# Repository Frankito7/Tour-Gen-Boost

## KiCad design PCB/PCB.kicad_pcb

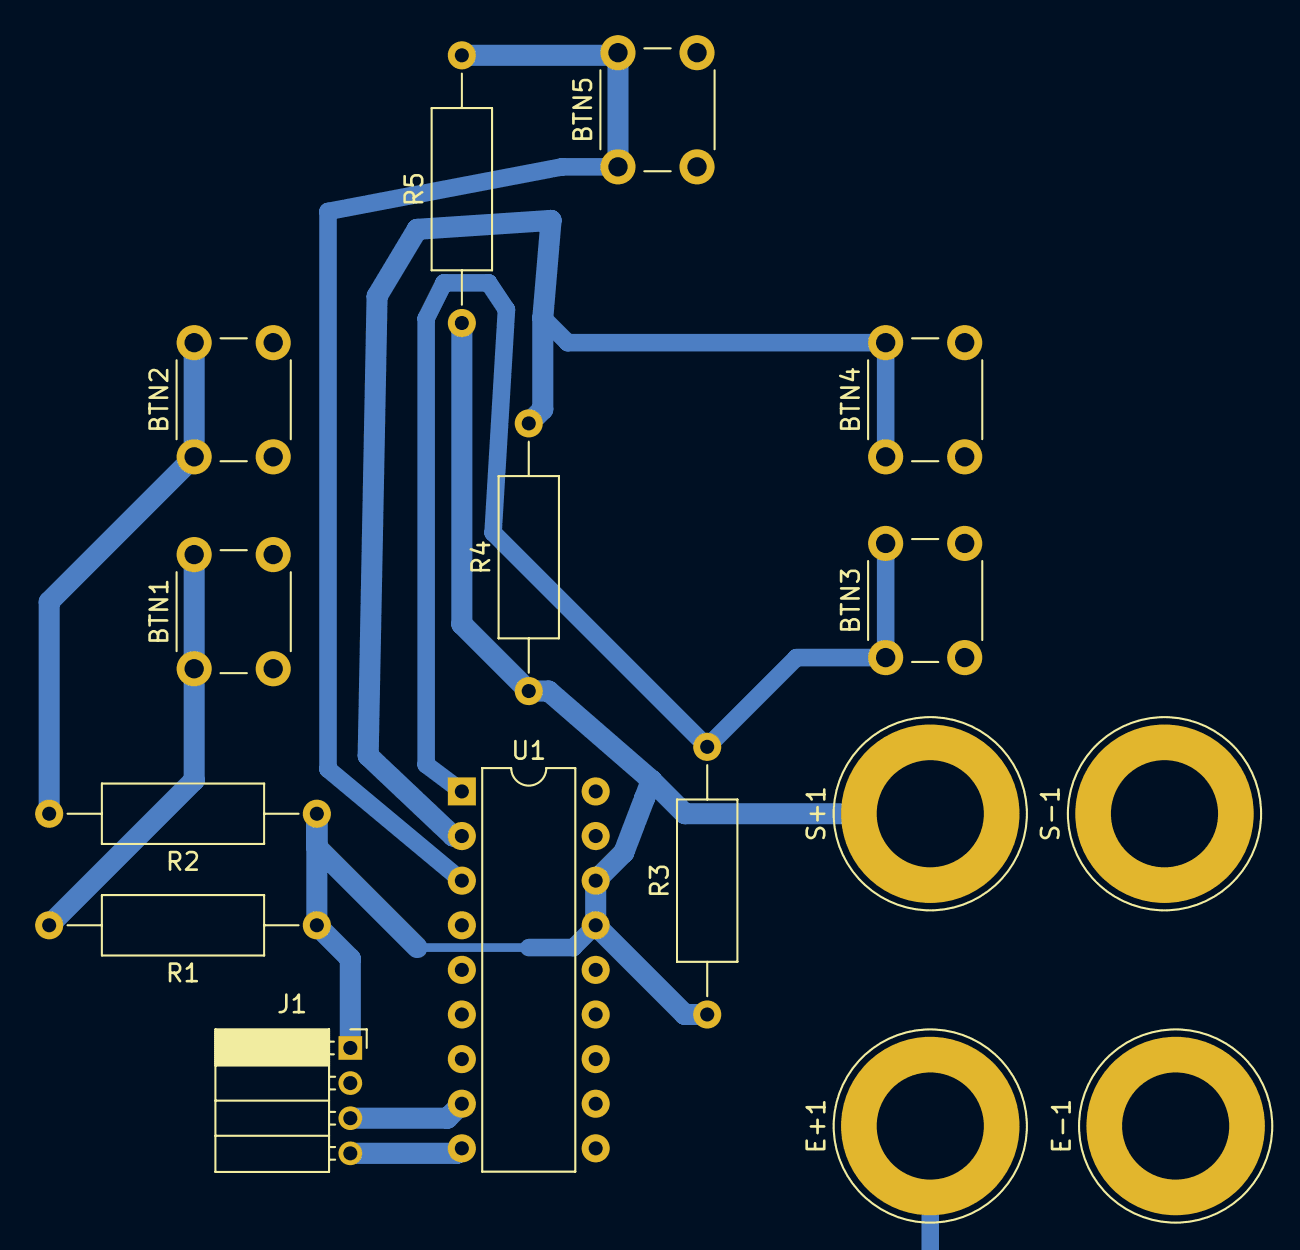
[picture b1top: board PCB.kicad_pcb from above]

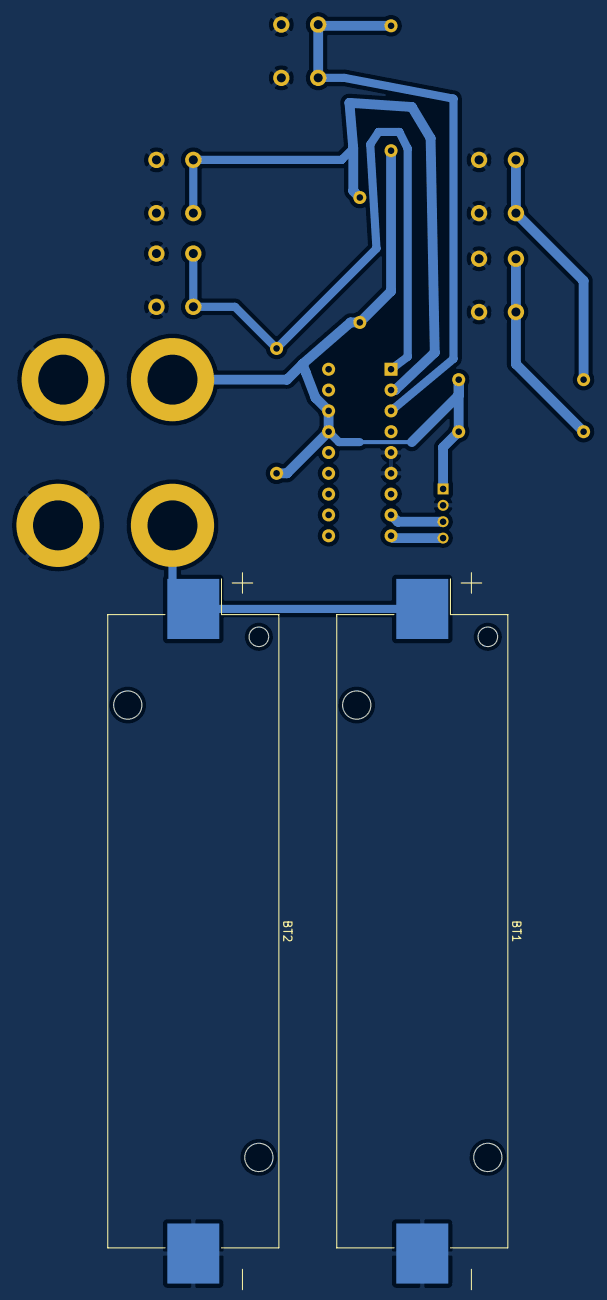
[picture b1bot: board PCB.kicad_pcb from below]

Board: 2 copper layers, 18 parts (2 on the bottom side), 10 nets.

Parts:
BT1, BT2: 3.7V; BatteryHolder_Keystone_1042_1x18650
BTN1, BTN2, BTN3, BTN4, BTN5: SW; SW_PUSH_6mm_H13mm
E+1: Conn_01x01_Female; Banana_Jack_1Pin
E-1: Conn_01x01_Female; Banana_Jack_1Pin
J1: HC-06; PinSocket_1x04_P2.00mm_Horizontal
R1, R2, R3, R4, R5: 10k; R_Axial_DIN0309_L9.0mm_D3.2mm_P15.24mm_Horizontal
S+1: Conn_01x01_Female; Banana_Jack_1Pin
S-1: Conn_01x01_Female; Banana_Jack_1Pin
U1: PIC16F628A-ISS; DIP-18_W7.62mm

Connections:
GND: BT1.2, BT2.2, BTN1.2, BTN2.2, BTN3.2, BTN4.2, BTN5.2, E-1.1, J1.2, S-1.1, U1.5, U1.6
unnamed: BT1.1, BT2.1, E+1.1
unnamed: BTN1.1, R1.2
unnamed: BTN2.1, R2.2
unnamed: BTN3.1, R3.2, U1.1
unnamed: BTN4.1, R4.2, U1.2
unnamed: BTN5.1, R5.2, U1.3
unnamed: J1.1, R1.1, R2.1, R3.1, R4.1, R5.1, S+1.1, U1.15, U1.16
unnamed: J1.3, U1.8
unnamed: J1.4, U1.9

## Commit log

2020-09-01 Commit 1
2020-11-17 Control Remoto
2020-11-17 Documentacion 1
2020-11-17 PCB KiCAD
2020-11-17 Proteus
